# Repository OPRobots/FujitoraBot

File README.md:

# FujitoraBot
Robot siguelineas MAS RAPIDO DE ESPAÑA!! con motores brushless, succión centrifuga y STM32F4

## Hardware
- STM32F405RGT6
- ESC 4in1 BlHeli 14A
- 2x Motores Brushless 1306 2700KVs
- 1x Motor brushless 1104 4000KVs (succión)
- DIP Switch 2p SMD
- LiPo 3S 380 mAh
- 16x sensores QRE1113
- Ruedas Scaleauto Procomp 1
- Chasis de PCB con soportes de motores y ventilador en Nylon PA12 SLS

## Software
- Programado con VSCode y PlatformIO con LibOpenCM3
- Disponibles programas de competición

### Versión Robotracer

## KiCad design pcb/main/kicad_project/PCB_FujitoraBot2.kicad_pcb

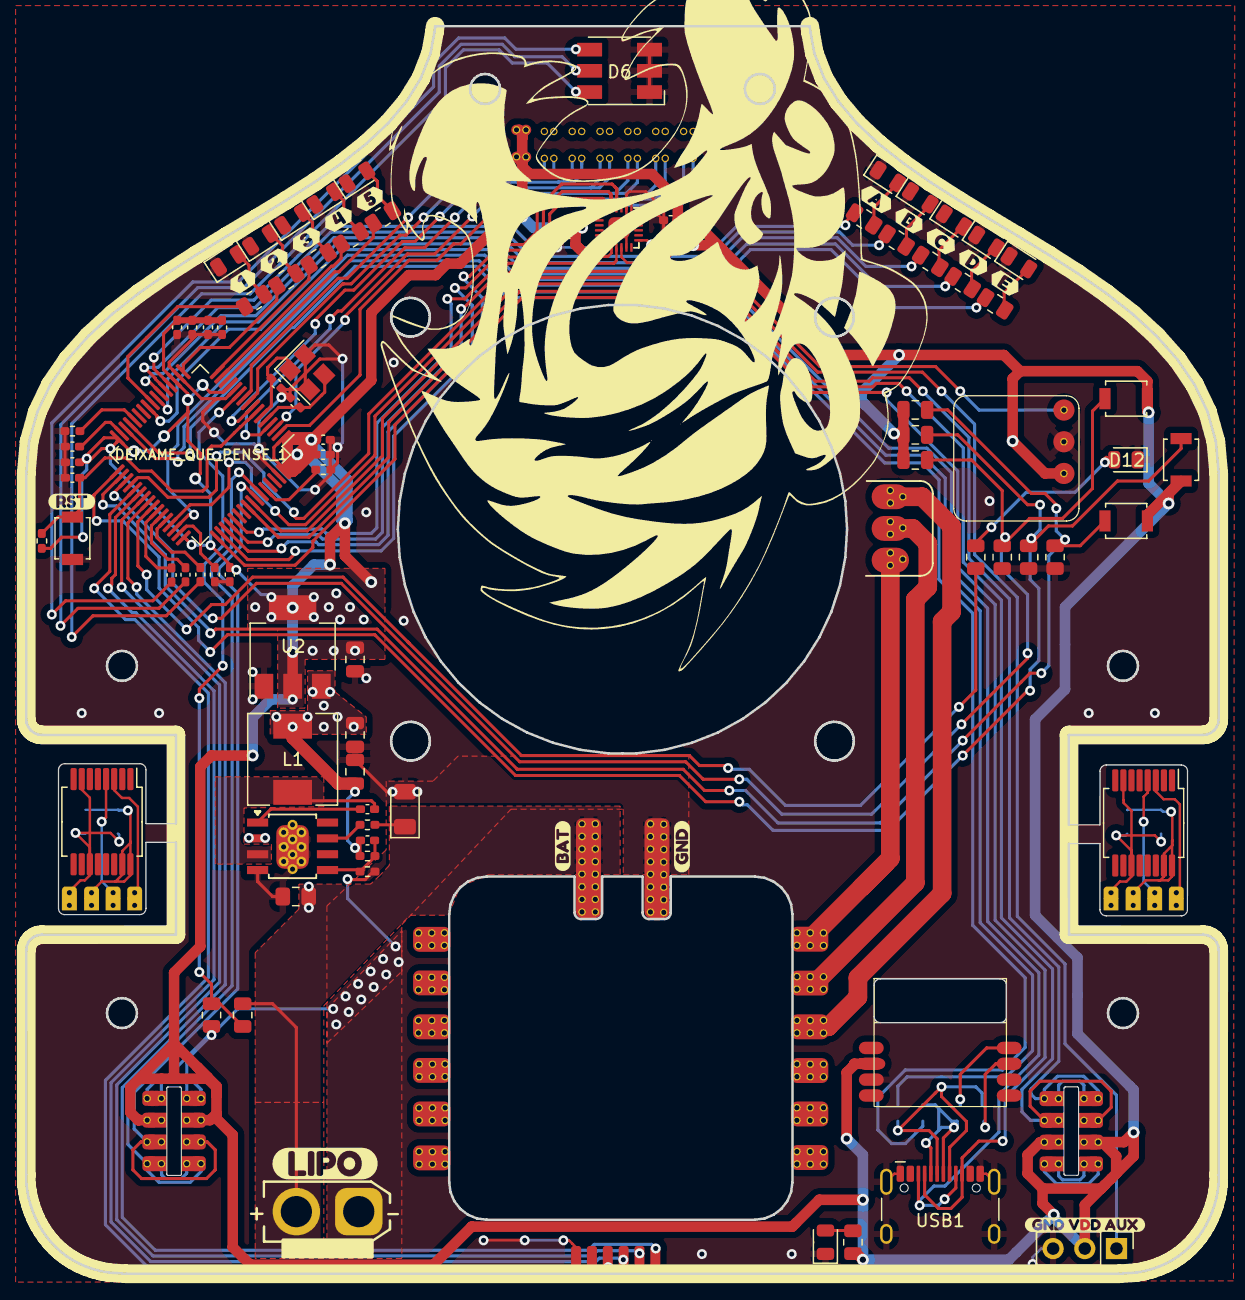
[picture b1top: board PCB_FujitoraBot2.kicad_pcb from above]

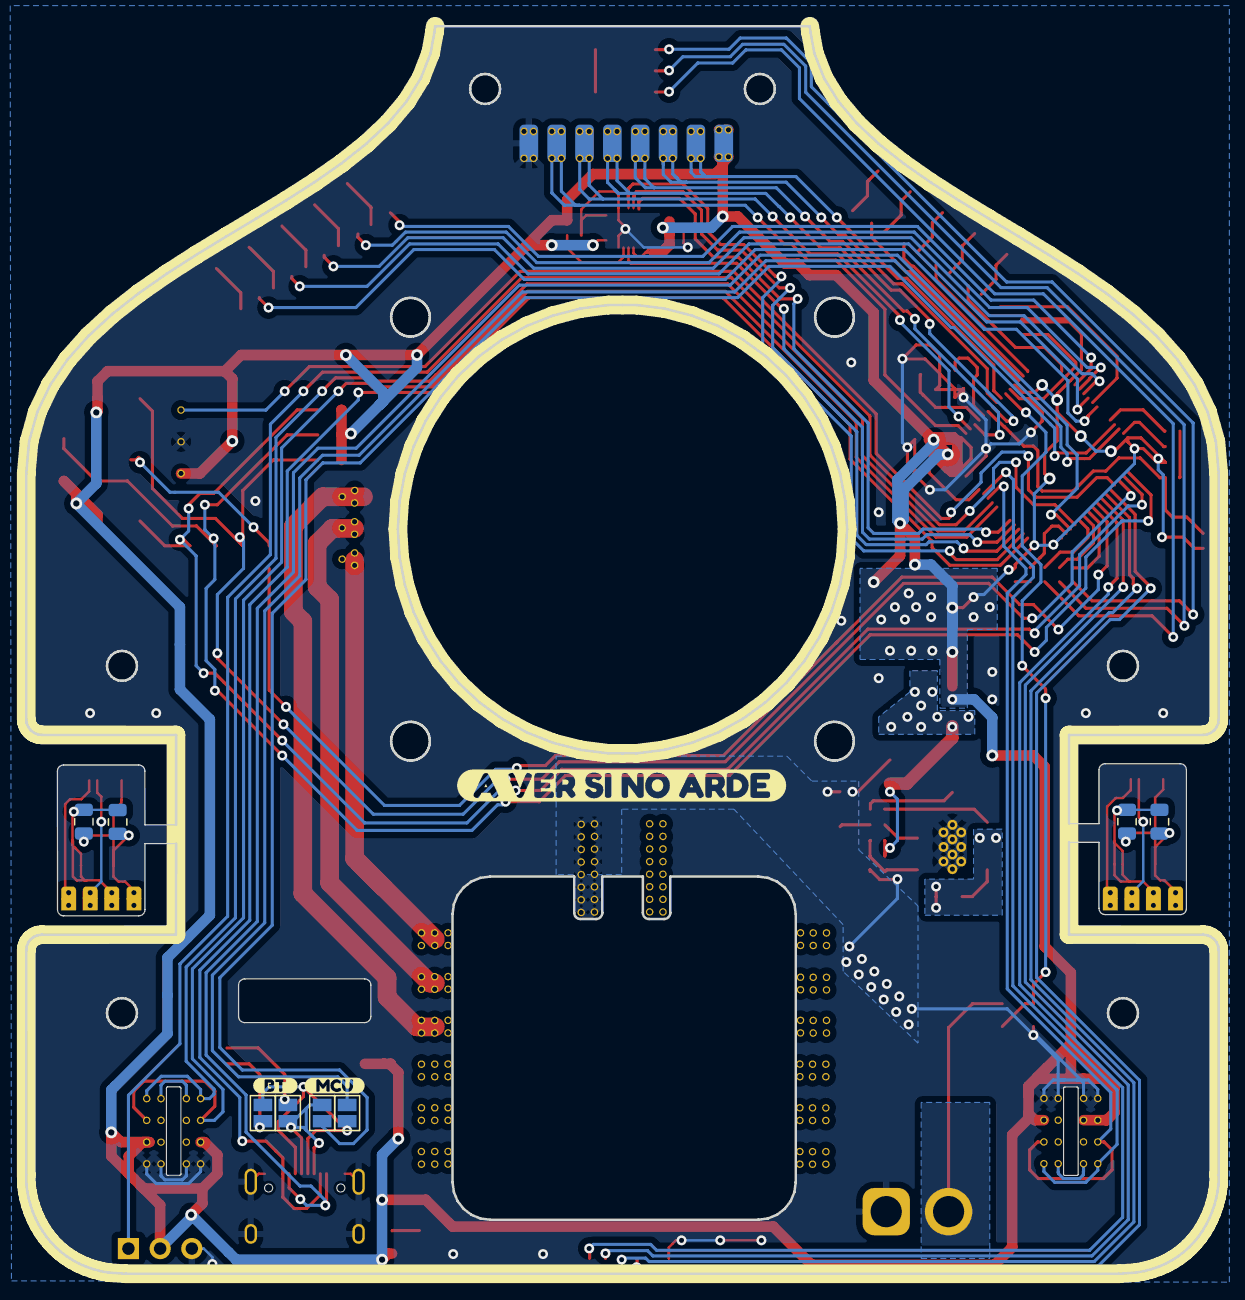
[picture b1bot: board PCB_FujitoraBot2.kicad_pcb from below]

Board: 2 copper layers, 95.6 x 100.0 mm, 117 parts (12 on the bottom side), 88 nets.

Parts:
BATT_1: Conn_01x02_Female; XT30 connector
BT1: Bluetooth_BLE_1x1cm
C1, C20: 4.7uF; C_0402_1005Metric_Pad0.74x0.62mm_HandSolder
C2, C3, C7, C10, C11, C15, C17: 0.1uF; C_0402_1005Metric_Pad0.74x0.62mm_HandSolder
C4, C9: 2.2uF; C_0402_1005Metric_Pad0.74x0.62mm_HandSolder
C5: 20uF; C_0402_1005Metric_Pad0.74x0.62mm_HandSolder
C6: 20pF; C_0402_1005Metric_Pad0.74x0.62mm_HandSolder
C8, C12: 1uF; C_0402_1005Metric_Pad0.74x0.62mm_HandSolder
C13, C18: 1uF; C_0805_2012Metric
C14, C19: 0.1uF; C_0805_2012Metric
C16: 0.01uF; C_0402_1005Metric_Pad0.74x0.62mm_HandSolder
CR1, CR2, CR3, CR7, CR8: 0.1uF; C_0805_2012Metric
CR4, CR5, CR9: 0.1uF; C_0402_1005Metric_Pad0.74x0.62mm_HandSolder
CR6: 0.1uF; C_0805_2012Metric_Pad1.18x1.45mm_HandSolder
CR10: 10uF; C_0805_2012Metric
D1, D2, D3, D4, D5, D7, D8, D9, D10, D11, D12, D13: LED; LED_0805_2012Metric
D6: LED_RGB; LED_RGB_5050-6
D14: D; D_1206_3216Metric
DC-DC1: SOP8_with_gnd_pad
DEIXAME_QUE_PENSE_1: STM32F405RGT6; LQFP-64_10x10mm_P0.5mm
ESC1: ESC_x4_15A; Fujitora_ESC
IC1, IC2: AS5040; SSOP-16_5.3x6.2mm_P0.65mm
J1: MORRO1; Fujitora_pads_morro
JP1, JP2, JP3, JP4: SolderJumper_2_Open; SolderJumper-2_P1.3mm_Open_Pad1.0x1.5mm
J_ENC_1, J_ENC_2: Conn_01x04_Socket; FujitoraBot2_PCBmain_Encoder
J_ENC_1_CONN1, J_ENC_2_CONN1: Conn_01x04_Pin; FujitoraBot2_PCBmodule_encoder
J_ESC1: Conn_01x06_Female; Fujitora_pads_ESC
L1: L; L_Wuerth_HCM-7050
MODULO_START_STOP1: Conn_01x03_Female; IR_Start
MOTOR_1: Conn_01x03_Female; PinHeader_1x03_P2.54mm_Vertical
PIN_AUXILIAR1: Conn_01x03_Female; PinHeader_1x03_P2.54mm_Vertical
R1, R2, R3, R4, R5, R9, R10, R11, R12, R13, R15: 330; R_0805_2012Metric
R6, R7, R8: 330; C_0402_1005Metric_Pad0.74x0.62mm_HandSolder
R14: 47k; R_0402_1005Metric_Pad0.72x0.64mm_HandSolder
R16: 1K; R_0805_2012Metric
R17, R25: 47K; R_0402_1005Metric_Pad0.72x0.64mm_HandSolder
R18, R19, R20, R23, R24: 47K; R_0805_2012Metric
R28: 45K; R_0402_1005Metric_Pad0.72x0.64mm_HandSolder
R29: 100k; R_0402_1005Metric_Pad0.72x0.64mm_HandSolder
R30: 60k; R_0402_1005Metric_Pad0.72x0.64mm_HandSolder
SW1, SW2, SW3: SW_Push; SW_SPST_B3U-1000P
SW4: SW_Reset; SW_SPST_B3U-1000P
U1: MPU-6500; FujitoraBot2_giro_MPU6500
U2: LM1117MP-3.3; SOT-223-3_TabPin2
USB1: HRO-TYPE-C-31-M-12; USB-C ST-Link USART
Y1: Crystal_GND24; Crystal_SMD_TXC_7M-4Pin_3.2x2.5mm
kibuzzard-66B8D5B6: G***; kibuzzard-66B8D5B6
kibuzzard-66B8D6B0: G***; kibuzzard-66B8D6B0
kibuzzard-66B8D59D: G***; kibuzzard-66B8D59D
kibuzzard-66B8D625: G***; kibuzzard-66B8D625
kibuzzard-66B8D672: G***; kibuzzard-66B8D672
kibuzzard-66B8D700: G***; kibuzzard-66B8D700
kibuzzard-66B8DA7F: G***; kibuzzard-66B8DA7F
kibuzzard-66B8DA98: G***; kibuzzard-66B8DA98
kibuzzard-66B8DBE7: G***; kibuzzard-66B8DBE7
kibuzzard-66B8DBFF: G***; kibuzzard-66B8DBFF
kibuzzard-66B8DC0B: G***; kibuzzard-66B8DC0B
kibuzzard-66B8DC05: G***; kibuzzard-66B8DC05
kibuzzard-66B8DC13: G***; kibuzzard-66B8DC13
kibuzzard-66B8DD07: G***; kibuzzard-66B8DD07
kibuzzard-66B8DD11: G***; kibuzzard-66B8DD11
kibuzzard-66B8DD29: G***; kibuzzard-66B8DD29
kibuzzard-66B8DD65: G***; kibuzzard-66B8DD65
kibuzzard-66B8DD76: G***; kibuzzard-66B8DD76

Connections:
+3V3: BT1.2 (VCC), C1.2, C2.2, C3.2, C7.2, C8.2, C10.2, C11.2, C12.2, C15.2, C16.2, C20.2, CR1.1, CR2.1, CR3.1, CR10.1, DEIXAME_QUE_PENSE_1.1 (VBAT), DEIXAME_QUE_PENSE_1.13 (VDDA), DEIXAME_QUE_PENSE_1.19 (VDD), DEIXAME_QUE_PENSE_1.32 (VDD), DEIXAME_QUE_PENSE_1.48 (VDD), DEIXAME_QUE_PENSE_1.64 (VDD), J1.8, J_ENC_1.2, J_ENC_2.2, MODULO_START_STOP1.1, PIN_AUXILIAR1.2, R14.2, R16.1, SW1.2, SW2.2, SW3.2, U1.8 (VDDIO), U1.13 (VDD), U2.2 (VO)
+5V: CR7.2, CR8.1, CR9.1, L1.2, R30.1, U2.3 (VI)
/ANLG_BAT: DEIXAME_QUE_PENSE_1.11 (PC3), R23.2, R24.1
/AUX: DEIXAME_QUE_PENSE_1.45 (PA12), PIN_AUXILIAR1.1
/BATT: BATT_1.2, CR6.2, D14.1 (K), DC-DC1.2 (VIN), ESC1.20 (VCC), R23.1, R29.2
/BOOT: DEIXAME_QUE_PENSE_1.60 (BOOT0), R17.1
/ENC_1_3.3: C13.1, C14.1, IC1.15 (VDD3V3), IC1.16 (VDD5V), J_ENC_1_CONN1.2
/ENC_1_A: DEIXAME_QUE_PENSE_1.59 (PB7), J_ENC_1.4
/ENC_1_A_CONN: IC1.3 (A_LSB_U), J_ENC_1_CONN1.4
/ENC_1_B: DEIXAME_QUE_PENSE_1.58 (PB6), J_ENC_1.3
/ENC_1_B_CONN: IC1.4 (B_DIR_V), J_ENC_1_CONN1.3
/ENC_1_GND: C13.2, C14.2, IC1.7 (VSS), IC1.11 (CSN), J_ENC_1_CONN1.1
/ENC_2_3.3: C18.1, C19.1, IC2.15 (VDD3V3), IC2.16 (VDD5V), J_ENC_2_CONN1.2
/ENC_2_A: DEIXAME_QUE_PENSE_1.57 (PB5), J_ENC_2.4
/ENC_2_A_CONN: IC2.3 (A_LSB_U), J_ENC_2_CONN1.4
/ENC_2_B: DEIXAME_QUE_PENSE_1.56 (PB4), J_ENC_2.3
/ENC_2_B_CONN: IC2.4 (B_DIR_V), J_ENC_2_CONN1.3
/ENC_2_GND: C18.2, C19.2, IC2.7 (VSS), IC2.11 (CSN), J_ENC_2_CONN1.1
/ESC_M1_R: ESC1.7 (M3_R), MOTOR_1.3
/ESC_M1_S: ESC1.8 (M3_S), MOTOR_1.2
/ESC_M1_T: ESC1.9 (M3_T), MOTOR_1.1
/LED_1: DEIXAME_QUE_PENSE_1.14 (PA0), R1.1
/LED_2: DEIXAME_QUE_PENSE_1.15 (PA1), R2.1
/LED_3: DEIXAME_QUE_PENSE_1.16 (PA2), R3.1
/LED_4: DEIXAME_QUE_PENSE_1.17 (PA3), R4.1
/LED_5: DEIXAME_QUE_PENSE_1.20 (PA4), R9.1
/LED_6: DEIXAME_QUE_PENSE_1.21 (PA5), R10.1
/LED_7: DEIXAME_QUE_PENSE_1.22 (PA6), R11.1
/LED_8: DEIXAME_QUE_PENSE_1.23 (PA7), R12.1
/LED_9: DEIXAME_QUE_PENSE_1.24 (PC4), R5.1
/LED_10: DEIXAME_QUE_PENSE_1.25 (PC5), R13.1
/LED_AUX: DEIXAME_QUE_PENSE_1.41 (PA8), R15.1
/MENU_ABAJO: CR2.2, DEIXAME_QUE_PENSE_1.34 (PB13), R19.1, SW2.1
/MENU_ARRIBA: CR1.2, DEIXAME_QUE_PENSE_1.35 (PB14), R18.1, SW1.1
/MENU_ENTER: CR3.2, DEIXAME_QUE_PENSE_1.33 (PB12), R20.1, SW3.1
/MUX_A: DEIXAME_QUE_PENSE_1.2 (PC13), J1.2
/MUX_B: DEIXAME_QUE_PENSE_1.3 (PC14), J1.3
/MUX_C: DEIXAME_QUE_PENSE_1.4 (PC15), J1.4
/MotorD: DEIXAME_QUE_PENSE_1.37 (PC6), J_ESC1.3
/MotorI: DEIXAME_QUE_PENSE_1.38 (PC7), J_ESC1.4
/MotorS1: DEIXAME_QUE_PENSE_1.39 (PC8), J_ESC1.5
/MotorS2: DEIXAME_QUE_PENSE_1.40 (PC9), J_ESC1.6
/RGB_B: DEIXAME_QUE_PENSE_1.44 (PA11), R6.1
/RGB_G: DEIXAME_QUE_PENSE_1.43 (PA10), R7.1
/RGB_R: DEIXAME_QUE_PENSE_1.42 (PA9), R8.1
/RST: CR4.1, DEIXAME_QUE_PENSE_1.7 (NRST), R14.1, SW4.1
/RX: JP2.2 (B), JP4.2 (B), USB1.6 (DP1), USB1.8 (DP2)
/SPI_MISO: DEIXAME_QUE_PENSE_1.52 (PC11), U1.9 (AD0/SDO)
/SPI_MOSI: DEIXAME_QUE_PENSE_1.53 (PC12), U1.24 (SDA/SDI)
/SPI_NSS: DEIXAME_QUE_PENSE_1.50 (PA15), U1.22 (nCS)
/SPI_SCK: DEIXAME_QUE_PENSE_1.51 (PC10), U1.23 (SCL/SCLK)
/START_STOP: DEIXAME_QUE_PENSE_1.36 (PB15), MODULO_START_STOP1.3
/SWCLK: DEIXAME_QUE_PENSE_1.49 (PA14), USB1.4 (CC1), USB1.10 (CC2)
/SWDIO: DEIXAME_QUE_PENSE_1.46 (PA13), USB1.3 (SBU2), USB1.9 (SBU1)
/S_DE_X8: DEIXAME_QUE_PENSE_1.10 (PC2), J1.7
/S_FR_X8: DEIXAME_QUE_PENSE_1.9 (PC1), J1.6
/S_IZ_X8: DEIXAME_QUE_PENSE_1.8 (PC0), J1.5
/TX: JP1.2 (B), JP3.1 (A), USB1.5 (DN2), USB1.7 (DN1)
GND: BATT_1.1, BT1.3 (GND), C1.1, C2.1, C3.1, C4.1, C5.1, C6.1, C7.1, C8.1, C9.1, C10.1, C11.1, C12.1, C15.1, C16.1, C17.1, C20.1, CR4.2, CR6.1, CR7.1, CR8.2, CR10.2, D1.1 (K), D2.1 (K), D3.1 (K), D4.1 (K), D5.1 (K), D6.1 (RK), D6.2 (GK), D6.3 (BK), D7.1 (K), D8.1 (K), D9.1 (K), D10.1 (K), D11.1 (K), D12.1 (K), D13.1 (K), D14.2 (A), DC-DC1.4 (GND), DC-DC1.9 (EPAD), DEIXAME_QUE_PENSE_1.12 (VSSA), DEIXAME_QUE_PENSE_1.18 (VSS), DEIXAME_QUE_PENSE_1.63 (VSS), ESC1.19 (GND), J1.1, J_ENC_1.1, J_ENC_2.1, J_ESC1.1, MODULO_START_STOP1.2, PIN_AUXILIAR1.3, R17.2, R18.2, R19.2, R20.2, R24.2, R25.2, R28.1, SW4.2, U1.11 (FSYNC), U1.18 (GND), U1.20 (RESV), U2.1 (GND), USB1.1 (GND), USB1.12 (GND), USB1.13 (SHIELD), Y1.2, Y1.4
unnamed: BT1.8 (RX), JP3.2 (B)
unnamed: BT1.7 (TX), JP4.1 (A)
unnamed: D1.2 (A), R1.2
unnamed: D2.2 (A), R2.2
unnamed: D3.2 (A), R3.2
unnamed: D4.2 (A), R4.2
unnamed: D5.2 (A), R5.2
unnamed: D6.4 (BA), R8.2
unnamed: D6.5 (GA), R7.2
unnamed: D6.6 (RA), R6.2
unnamed: D7.2 (A), R9.2
unnamed: D8.2 (A), R10.2
unnamed: D9.2 (A), R11.2
unnamed: D10.2 (A), R12.2
unnamed: D11.2 (A), R13.2
unnamed: D12.2 (A), R15.2
unnamed: D13.2 (A), R16.2
unnamed: CR5.2, DC-DC1.1 (BST)
unnamed: DC-DC1.7 (EN), R29.1
unnamed: CR9.2, DC-DC1.5 (FB), R28.2, R30.2
unnamed: CR5.1, DC-DC1.3 (SW), L1.1
unnamed: DEIXAME_QUE_PENSE_1.28 (PB2/BOOT1), R25.1
unnamed: DEIXAME_QUE_PENSE_1.29 (PB10), JP1.1 (A)
unnamed: DEIXAME_QUE_PENSE_1.30 (PB11), JP2.1 (A)
unnamed: C5.2, DEIXAME_QUE_PENSE_1.5 (PH0/OSC_IN), Y1.3
unnamed: C6.2, DEIXAME_QUE_PENSE_1.6 (PH1/OSC_OUT), Y1.1
unnamed: C9.2, DEIXAME_QUE_PENSE_1.31 (VCAP_1)
unnamed: C4.2, DEIXAME_QUE_PENSE_1.47 (VCAP_2)
unnamed: C17.2, U1.10 (REGOUT)

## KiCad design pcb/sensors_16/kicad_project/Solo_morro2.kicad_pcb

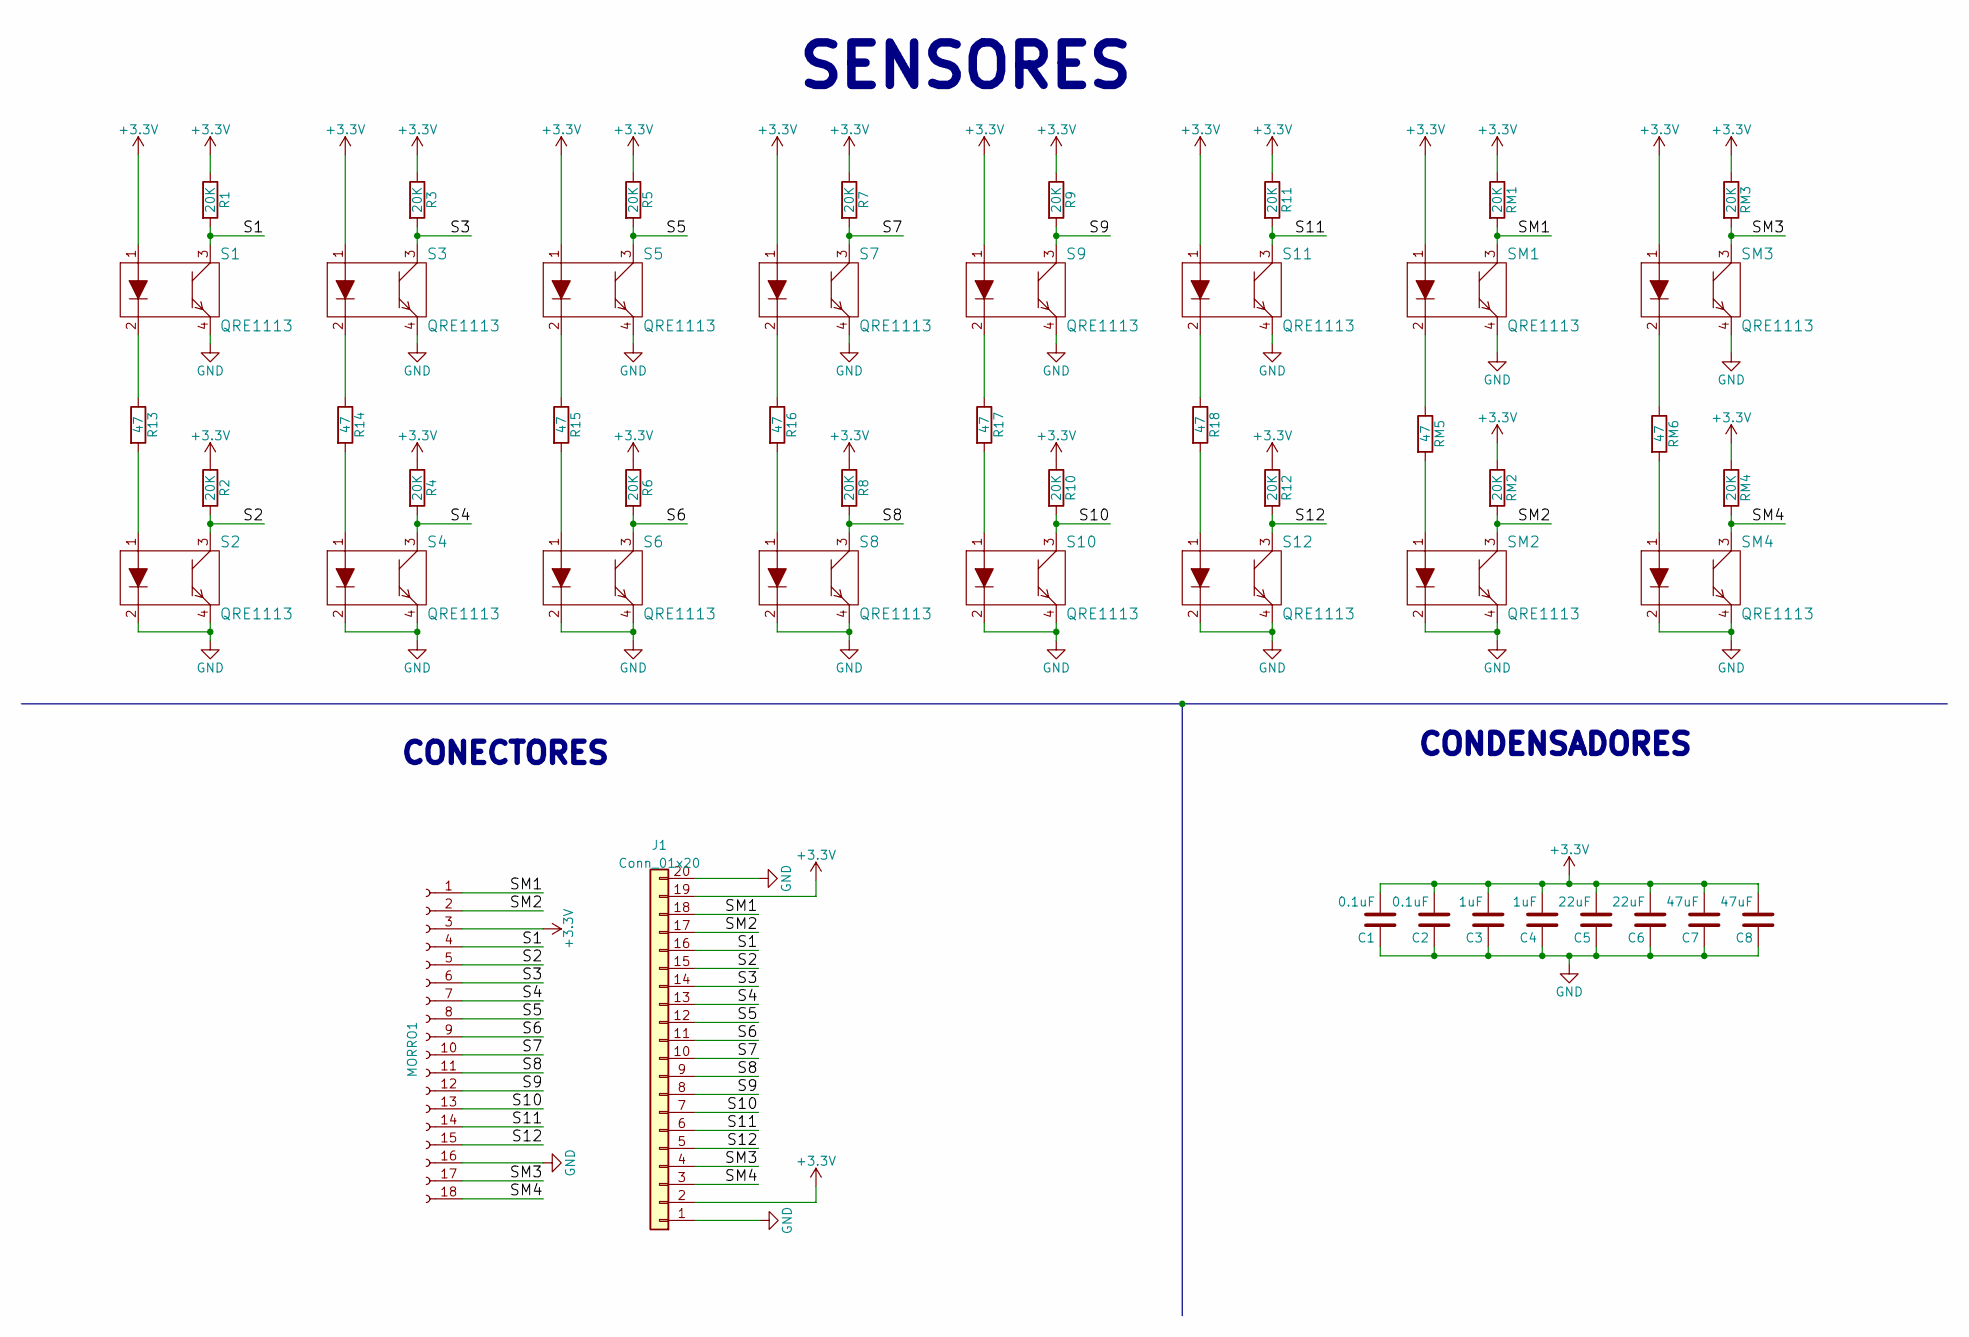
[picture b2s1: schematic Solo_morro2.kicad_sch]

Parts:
C1, C2: 0.1uF; C_0805_2012Metric
C3, C4: 1uF; C_0805_2012Metric
C5, C6: 22uF; C_0805_2012Metric
C7, C8: 47uF; C_0805_2012Metric
J1: Conn_01x20; Pines_fuji_morro2
MORRO1: Conn_01x14_Female; conn_morro_fuji_new
R1, R2, R3, R4, R5, R6, R7, R8, R9, R10, R11, R12: 20K; R_0805_2012Metric
R13, R14, R15, R16, R17, R18: 47; R_0805_2012Metric
RM1, RM2, RM3, RM4: 20K; R_0805_2012Metric
RM5, RM6: 47; R_0805_2012Metric
S1, S2, S3, S4, S5, S6, S7, S8, S9, S10, S11, S12: QRE1113; qre1113_fuji_morro2
SM1, SM2, SM3, SM4: QRE1113; qre1113_fuji_morro2

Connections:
+3V3: C1.2, C2.2, C3.2, C4.2, C5.2, C6.2, C7.2, C8.2, J1.2, J1.19, MORRO1.3, R1.1, R2.1, R3.1, R4.1, R5.1, R6.1, R7.1, R8.1, R9.1, R10.1, R11.1, R12.1, RM1.1, RM2.1, RM3.1, RM4.1, S1.1, S3.1, S5.1, S7.1, S9.1, S11.1, SM1.1, SM3.1
/S1: J1.16, MORRO1.4, R1.2, S1.3
/S2: J1.15, MORRO1.5, R2.2, S2.3
/S3: J1.14, MORRO1.6, R3.2, S3.3
/S4: J1.13, MORRO1.7, R4.2, S4.3
/S5: J1.12, MORRO1.8, R5.2, S5.3
/S6: J1.11, MORRO1.9, R6.2, S6.3
/S7: J1.10, MORRO1.10, R7.2, S7.3
/S8: J1.9, MORRO1.11, R8.2, S8.3
/S9: J1.8, MORRO1.12, R9.2, S9.3
/S10: J1.7, MORRO1.13, R10.2, S10.3
/S11: J1.6, MORRO1.14, R11.2, S11.3
/S12: J1.5, MORRO1.15, R12.2, S12.3
/SM1: J1.18, MORRO1.1, RM1.2, SM1.3
/SM2: J1.17, MORRO1.2, RM2.2, SM2.3
/SM3: J1.4, MORRO1.17, RM3.2, SM3.3
/SM4: J1.3, MORRO1.18, RM4.2, SM4.3
GND: C1.1, C2.1, C3.1, C4.1, C5.1, C6.1, C7.1, C8.1, J1.1, J1.20, MORRO1.16, S1.4, S2.2, S2.4, S3.4, S4.2, S4.4, S5.4, S6.2, S6.4, S7.4, S8.2, S8.4, S9.4, S10.2, S10.4, S11.4, S12.2, S12.4, SM1.4, SM2.2, SM2.4, SM3.4, SM4.2, SM4.4
unnamed: R13.1, S1.2
unnamed: R13.2, S2.1
unnamed: R14.1, S3.2
unnamed: R14.2, S4.1
unnamed: R15.1, S5.2
unnamed: R15.2, S6.1
unnamed: R16.1, S7.2
unnamed: R16.2, S8.1
unnamed: R17.1, S9.2
unnamed: R17.2, S10.1
unnamed: R18.1, S11.2
unnamed: R18.2, S12.1
unnamed: RM5.1, SM1.2
unnamed: RM5.2, SM2.1
unnamed: RM6.1, SM3.2
unnamed: RM6.2, SM4.1

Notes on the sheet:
SENSORES
CONECTORES
CONDENSADORES

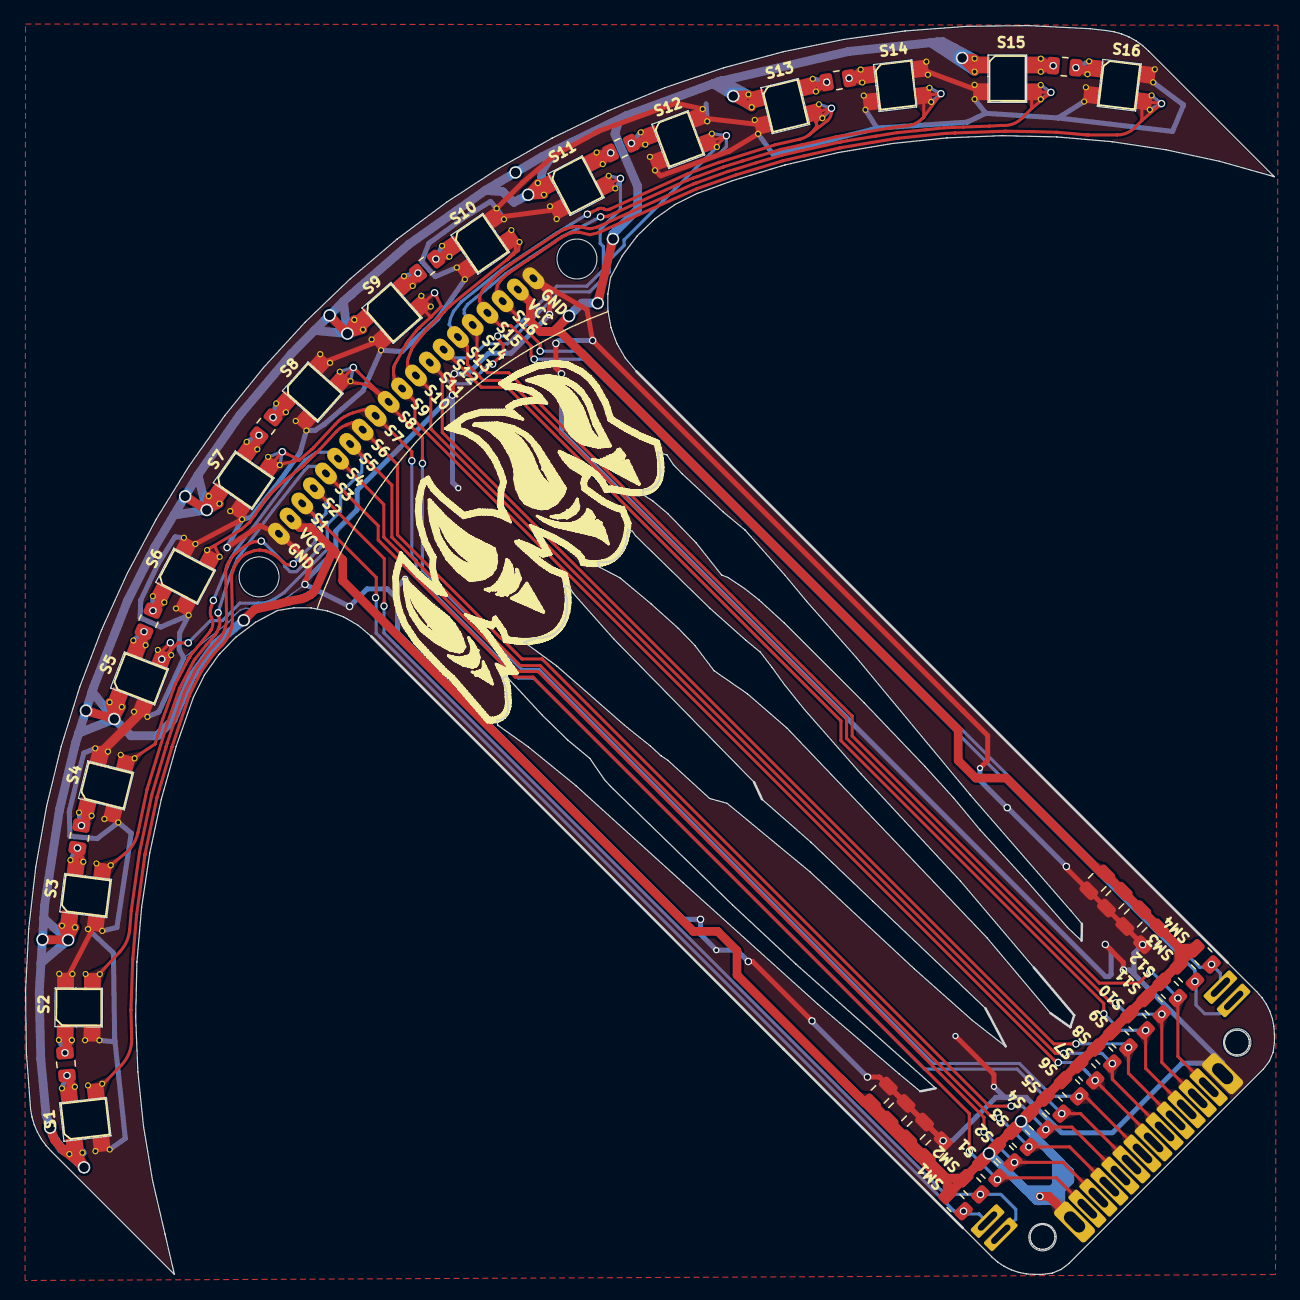
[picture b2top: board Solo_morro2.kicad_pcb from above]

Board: 2 copper layers, 100.0 x 100.0 mm, 50 parts (1 on the bottom side), 34 nets.

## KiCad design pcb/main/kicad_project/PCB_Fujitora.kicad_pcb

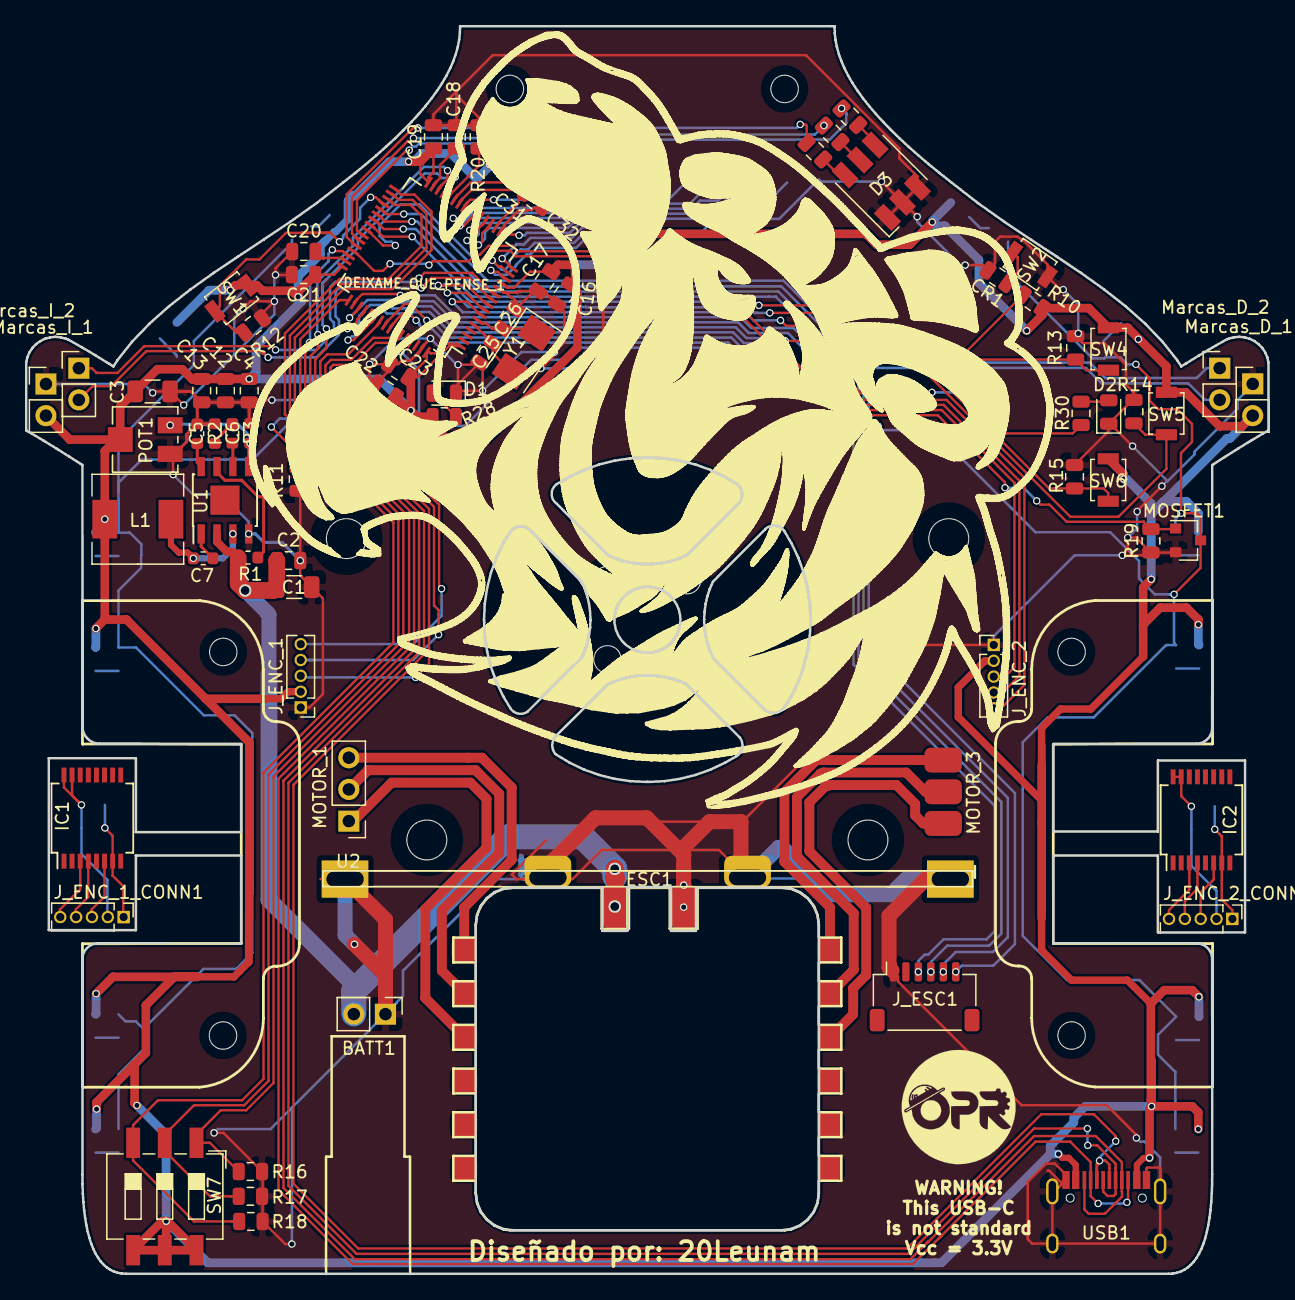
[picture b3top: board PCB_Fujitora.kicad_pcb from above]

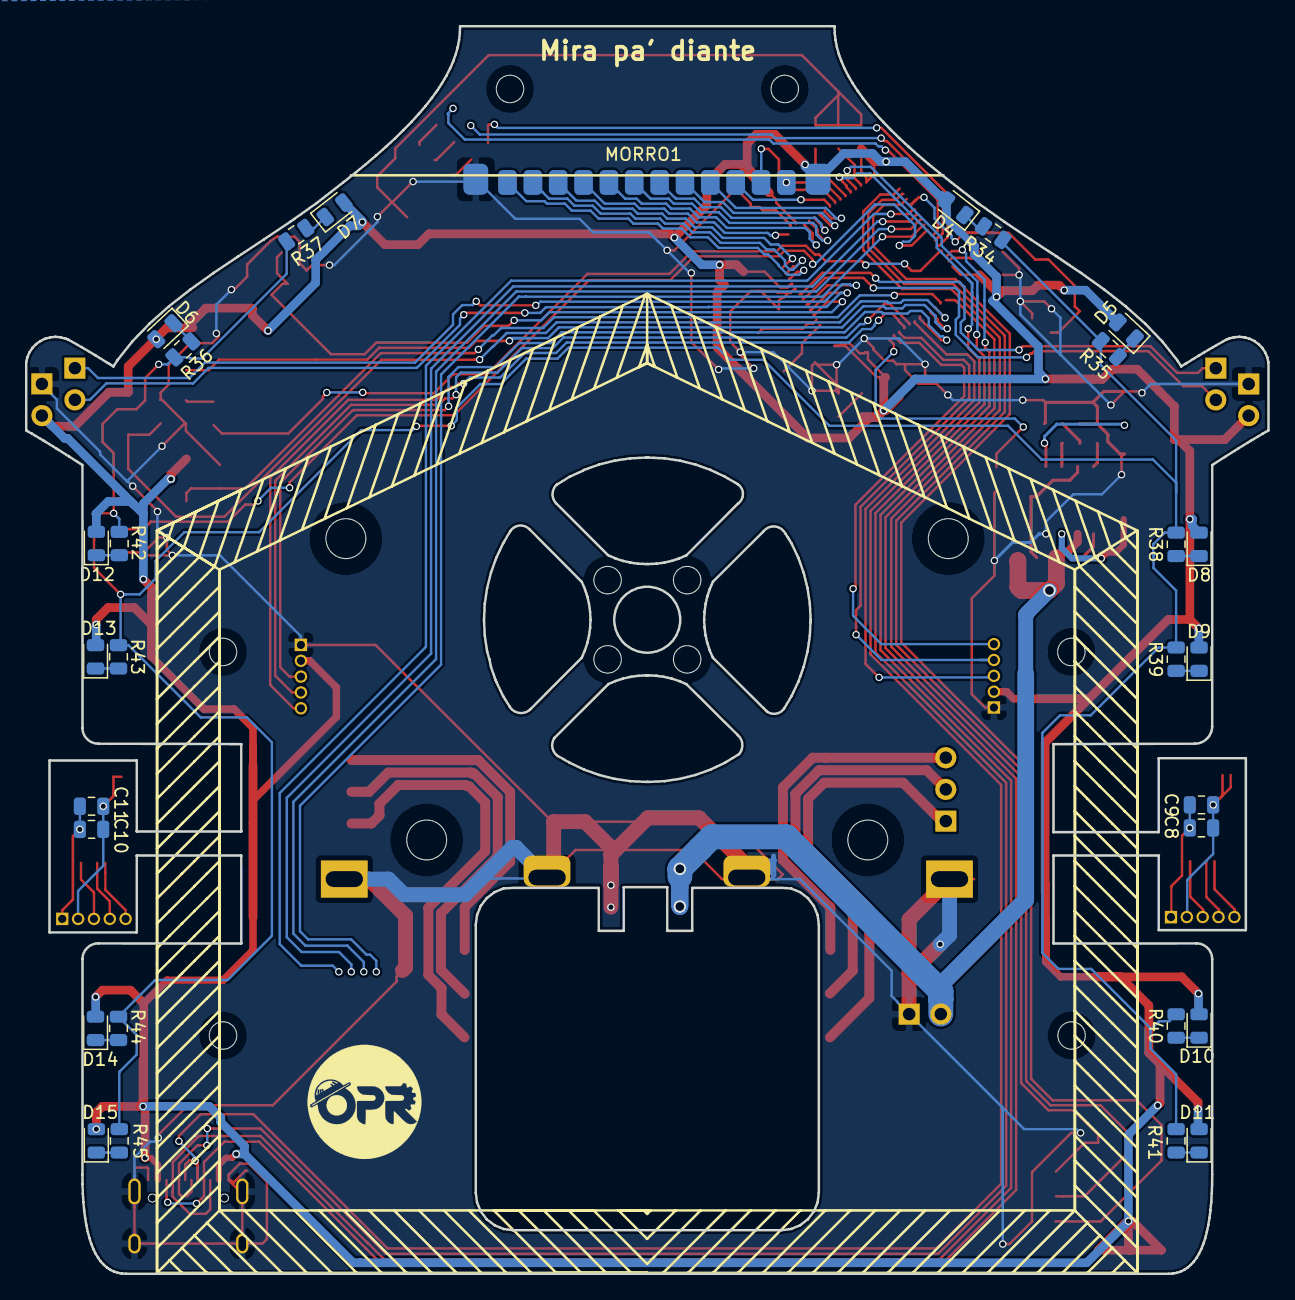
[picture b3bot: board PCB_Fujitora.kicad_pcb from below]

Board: 2 copper layers, 99.6 x 100.0 mm, 102 parts (29 on the bottom side), 93 nets.

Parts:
BATT1: Conn_01x02; PinHeader_1x02_P2.54mm_Vertical
C1: 10uF; C_1206_3216Metric
C2: 10uF; C_0805_2012Metric
C3: 22uF; C_1206_3216Metric
C4: 22uF; C_0805_2012Metric
C5: 0.1uF; C_0603_1608Metric
C6: 3.9nF; C_0603_1608Metric
C7: 0.01uF; C_0603_1608Metric
C8, C10, C17, C32: 1uF; C_0805_2012Metric
C9, C11, C16, C19, C21, C23, C31: 0.1uF; C_0805_2012Metric
C12, C13: 47uF; C_0805_2012Metric
C18, C20: 2.2uF; C_0805_2012Metric
C22: 4.7uF; C_0805_2012Metric
C25: 20uF; C_0805_2012Metric
C26: 20pF; C_0805_2012Metric
CR1: 0.1uF; C_0805_2012Metric
D1, D2, D4, D5, D6, D7, D8, D9, D10, D11, D12, D13, D14, D15: LED; LED_0805_2012Metric
D3: LED_RGB; LED_RGB_5050-6
DEIXAME_QUE_PENSE_1: STM32F405RGT6; LQFP-64_10x10mm_P0.5mm
ESC1: ESC_x4_15A
IC1, IC2: AS5040; SSOP-16_5.3x6.2mm_P0.65mm
J_ENC_1, J_ENC_2: Conn_01x05_Female; PinHeader_1x05_P1.27mm_Vertical
J_ENC_1_CONN1, J_ENC_2_CONN1: Conn_01x05_Male; PinHeader_1x05_P1.27mm_Vertical
J_ESC1: Conn_01x06_Female; JST_SH_SM06B-SRSS-TB_1x06-1MP_P1.00mm_Horizontal
L1: 10uH; L_Wuerth_HCM-7050
MORRO1: Conn_01x14_Female; conn_morro_fuji_new
MOSFET1: MOSFET-N; SOT-23
MOTOR_1: Conn_01x03_Female; PinHeader_1x03_P2.54mm_Vertical
MOTOR_3: Conn_01x03_Female; Conn_SMDx3_2.54
Marcas_D_1, Marcas_D_2: Conn_01x02_Female; PinHeader_1x02_P2.54mm_Vertical
Marcas_I_1, Marcas_I_2: Conn_01x02_Female; PinHeader_1x02_P2.54mm_Vertical
POT1: 50K; Potentiometer_Vishay_TS53YJ_Vertical
R1: 100K; R_0603_1608Metric
R2: 6.8K; R_0603_1608Metric
R3: 10K; R_0603_1608Metric
R10: 47k; R_0805_2012Metric
R11, R12, R13, R14, R15, R16, R17, R18, R19, R20: 47K; R_0805_2012Metric
R28: 1K; R_0805_2012Metric
R30, R31, R32, R33, R34, R35, R36, R37, R38, R39, R40, R41, R42, R43, R44, R45: 330; R_0805_2012Metric
SW1, SW4, SW5, SW6: SW_Push; SW_SPST_B3U-1000P
SW2: SW_Reset; SW_SPST_B3U-1000P
SW7: SW_DIP_x03; SW_DIP_SPSTx03_Slide_6.7x9.18mm_W8.61mm_P2.54mm_LowProfile
U1: MP2307; SOIC-8-1EP_3.9x4.9mm_P1.27mm_EP2.35x2.35mm
U2: Barra_anti-Flex; Barra_Anti-Flex
USB1: HRO-TYPE-C-31-M-12
Y1: Crystal; Crystal_SMD_5032-2Pin_5.0x3.2mm

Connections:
+3V3: C3.1, C4.1, C12.1, C13.1, C16.2, C17.2, C19.2, C21.2, C22.2, C23.2, C31.2, C32.2, D4.2, D5.2, D6.2, D7.2, D8.2, D9.2, D10.2, D11.2, D12.2, D13.2, D14.2, D15.2, DEIXAME_QUE_PENSE_1.1, DEIXAME_QUE_PENSE_1.13, DEIXAME_QUE_PENSE_1.19, DEIXAME_QUE_PENSE_1.32, DEIXAME_QUE_PENSE_1.48, DEIXAME_QUE_PENSE_1.64, J_ENC_1.2, J_ENC_2.2, L1.2, MORRO1.1, Marcas_D_1.2, Marcas_I_1.2, POT1.2, R10.2, R28.1, SW1.2, SW4.2, SW5.2, SW6.2, SW7.4, SW7.5, SW7.6, USB1.2, USB1.11
/BOOT: DEIXAME_QUE_PENSE_1.60, R11.1
/BTN_START: DEIXAME_QUE_PENSE_1.36, R12.1, SW1.1
/CONFIG_DOWN: DEIXAME_QUE_PENSE_1.50, R15.1, SW6.1
/CONFIG_MODO: DEIXAME_QUE_PENSE_1.52, R13.1, SW4.1
/CONFIG_UP: DEIXAME_QUE_PENSE_1.51, R14.1, SW5.1
/ENC_1_3.3: C8.1, C9.1, IC1.15, IC1.16, J_ENC_1_CONN1.2
/ENC_1_A: DEIXAME_QUE_PENSE_1.59, J_ENC_1.5
/ENC_1_A_CONN: IC1.3, J_ENC_1_CONN1.5
/ENC_1_B: DEIXAME_QUE_PENSE_1.58, J_ENC_1.4
/ENC_1_B_CONN: IC1.4, J_ENC_1_CONN1.4
/ENC_1_GND: C8.2, C9.2, IC1.7, J_ENC_1_CONN1.1
/ENC_1_I: DEIXAME_QUE_PENSE_1.55, J_ENC_1.3
/ENC_1_I_CONN: IC1.6, J_ENC_1_CONN1.3
/ENC_2_3.3: C10.1, C11.1, IC2.15, IC2.16, J_ENC_2_CONN1.2
/ENC_2_A: DEIXAME_QUE_PENSE_1.57, J_ENC_2.5
/ENC_2_A_CONN: IC2.3, J_ENC_2_CONN1.5
/ENC_2_B: DEIXAME_QUE_PENSE_1.56, J_ENC_2.4
/ENC_2_B_CONN: IC2.4, J_ENC_2_CONN1.4
/ENC_2_GND: C10.2, C11.2, IC2.7, J_ENC_2_CONN1.1
/ENC_2_I: DEIXAME_QUE_PENSE_1.54, J_ENC_2.3
/ENC_2_I_CONN: IC2.6, J_ENC_2_CONN1.3
/ESC_M1_R: ESC1.1, MOTOR_1.3
/ESC_M1_S: ESC1.2, MOTOR_1.2
/ESC_M1_T: ESC1.3, MOTOR_1.1
/ESC_M3_R: ESC1.7, MOTOR_3.3
/ESC_M3_S: ESC1.8, MOTOR_3.2
/ESC_M3_T: ESC1.9, MOTOR_3.1
/LED_AUX: DEIXAME_QUE_PENSE_1.45, R30.1
/LED_NEON: DEIXAME_QUE_PENSE_1.41, MOSFET1.1, R19.1
/MotorD: DEIXAME_QUE_PENSE_1.40, J_ESC1.3
/MotorI: DEIXAME_QUE_PENSE_1.39, J_ESC1.4
/MotorS1: DEIXAME_QUE_PENSE_1.38, J_ESC1.5
/MotorS2: DEIXAME_QUE_PENSE_1.37, J_ESC1.6
/POT_ESC: BATT1.2, C1.1, C2.1, ESC1.20, R1.1, U1.2
/RGB_B: DEIXAME_QUE_PENSE_1.44, R31.1
/RGB_G: DEIXAME_QUE_PENSE_1.43, R32.1
/RGB_R: DEIXAME_QUE_PENSE_1.42, R33.1
/RST: CR1.1, DEIXAME_QUE_PENSE_1.7, R10.1, SW2.1
/RX: DEIXAME_QUE_PENSE_1.30, USB1.6, USB1.8
/S1: DEIXAME_QUE_PENSE_1.27, MORRO1.2
/S2: DEIXAME_QUE_PENSE_1.26, MORRO1.3
/S3: DEIXAME_QUE_PENSE_1.25, MORRO1.4
/S4: DEIXAME_QUE_PENSE_1.24, MORRO1.5
/S5: DEIXAME_QUE_PENSE_1.23, MORRO1.6
/S6: DEIXAME_QUE_PENSE_1.22, MORRO1.7
/S7: DEIXAME_QUE_PENSE_1.21, MORRO1.8
/S8: DEIXAME_QUE_PENSE_1.20, MORRO1.9
/S9: DEIXAME_QUE_PENSE_1.17, MORRO1.10
/S10: DEIXAME_QUE_PENSE_1.16, MORRO1.11
/S11: DEIXAME_QUE_PENSE_1.15, MORRO1.12
/S12: DEIXAME_QUE_PENSE_1.14, MORRO1.13
/SM1: DEIXAME_QUE_PENSE_1.8, Marcas_D_2.2
/SM2: DEIXAME_QUE_PENSE_1.9, Marcas_D_2.1
/SM3: DEIXAME_QUE_PENSE_1.10, Marcas_I_2.2
/SM4: DEIXAME_QUE_PENSE_1.11, Marcas_I_2.1
/SWCLK: DEIXAME_QUE_PENSE_1.49, USB1.4, USB1.10
/SWDIO: DEIXAME_QUE_PENSE_1.46, USB1.3, USB1.9
/SW_1: DEIXAME_QUE_PENSE_1.33, R16.1, SW7.1
/SW_2: DEIXAME_QUE_PENSE_1.34, R17.1, SW7.2
/SW_3: DEIXAME_QUE_PENSE_1.35, R18.1, SW7.3
/TX: DEIXAME_QUE_PENSE_1.29, USB1.5, USB1.7
GND: BATT1.1, C1.2, C2.2, C3.2, C4.2, C5.2, C12.2, C13.2, C16.1, C17.1, C18.1, C19.1, C20.1, C21.1, C22.1, C23.1, C25.1, C26.1, C31.1, C32.1, CR1.2, D1.1, D2.1, D3.1, D3.2, D3.3, DEIXAME_QUE_PENSE_1.12, DEIXAME_QUE_PENSE_1.18, DEIXAME_QUE_PENSE_1.63, ESC1.19, J_ENC_1.1, J_ENC_2.1, J_ESC1.1, MORRO1.14, MOSFET1.2, Marcas_D_1.1, Marcas_I_1.1, POT1.3, R2.2, R3.2, R11.2, R12.2, R13.2, R14.2, R15.2, R16.2, R17.2, R18.2, R19.2, R20.2, SW2.2, U1.4, U2.1, U2.2, U2.3, U2.4, USB1.1, USB1.12, USB1.13
unnamed: C5.1, U1.8
unnamed: C6.1, U1.6
unnamed: C6.2, R2.1
unnamed: C7.1, L1.1, U1.3
unnamed: C7.2, U1.1
unnamed: C18.2, DEIXAME_QUE_PENSE_1.31
unnamed: C20.2, DEIXAME_QUE_PENSE_1.47
unnamed: C25.2, DEIXAME_QUE_PENSE_1.5, Y1.2
unnamed: C26.2, DEIXAME_QUE_PENSE_1.6, Y1.1
unnamed: D1.2, R28.2
unnamed: D2.2, R30.2
unnamed: D3.4, R33.2
unnamed: D3.5, R32.2
unnamed: D3.6, R31.2
unnamed: D4.1, R34.1
unnamed: D5.1, R35.1
unnamed: D6.1, R36.1
unnamed: D7.1, R37.1
unnamed: D8.1, R38.1
unnamed: D9.1, R39.1
unnamed: D10.1, R40.1
unnamed: D11.1, R41.1
unnamed: D12.1, R42.1
unnamed: D13.1, R43.1
unnamed: D14.1, R44.1
unnamed: D15.1, R45.1
unnamed: DEIXAME_QUE_PENSE_1.28, R20.1
unnamed: MOSFET1.3, R34.2, R35.2, R36.2, R37.2, R38.2, R39.2, R40.2, R41.2, R42.2, R43.2, R44.2, R45.2
unnamed: POT1.1, R3.1, U1.5
unnamed: R1.2, U1.7
